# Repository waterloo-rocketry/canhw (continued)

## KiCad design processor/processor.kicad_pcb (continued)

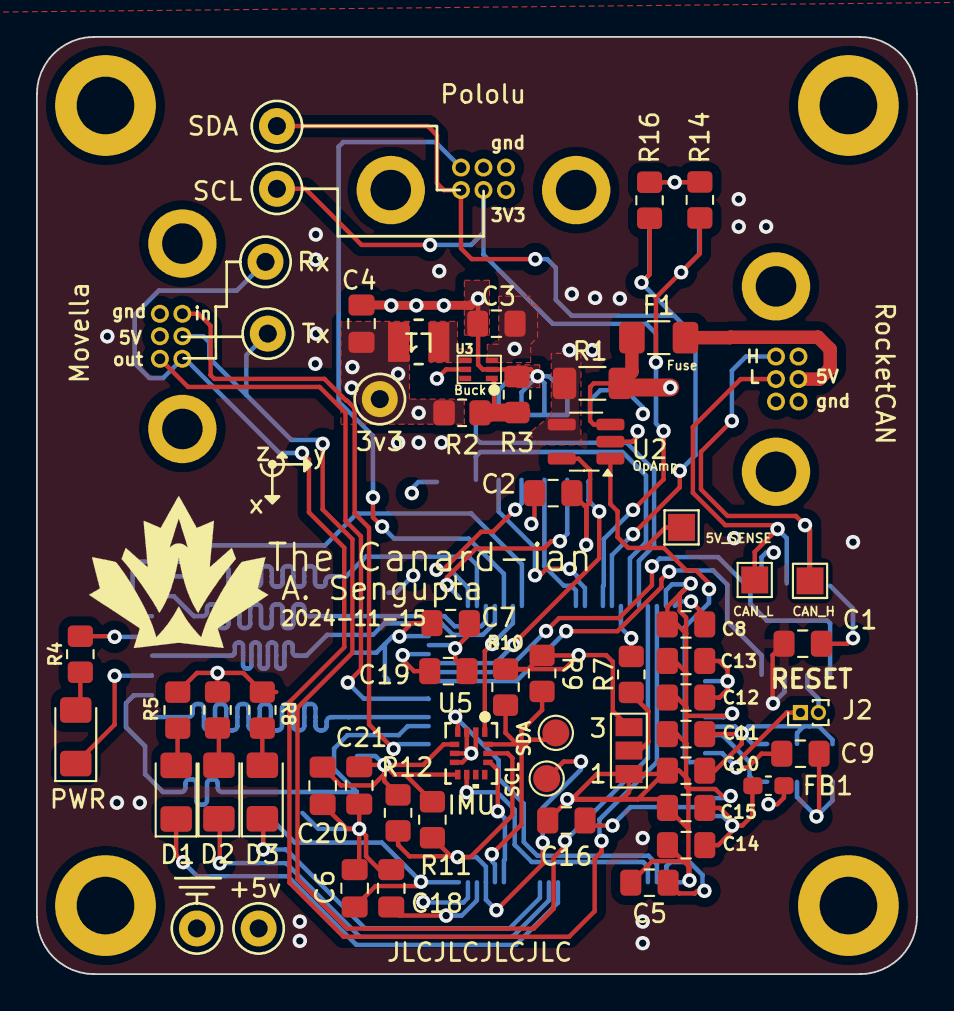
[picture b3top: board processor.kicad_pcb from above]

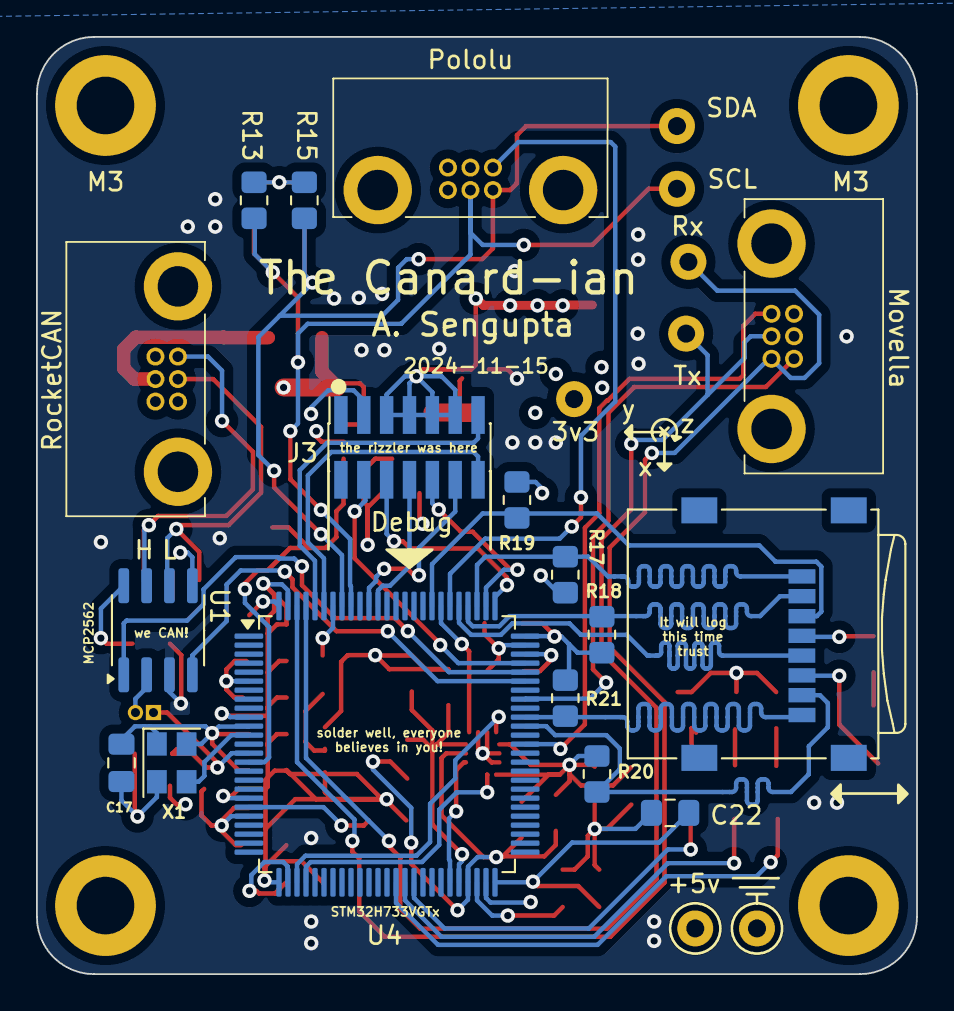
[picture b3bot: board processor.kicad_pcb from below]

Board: 4 copper layers, 48.9 x 52.1 mm, 79 parts (17 on the bottom side), 53 nets.

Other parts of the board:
H1, H2, H4: MountingHole_Pad; MountingHole_3.2mm_M3_DIN965_Pad

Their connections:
GND: H1.1, H2.1, H4.1; also elsewhere on the board

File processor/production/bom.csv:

Designator,Footprint,Quantity,Value,LCSC Part #
C1,0805,1,10uF,C15850
"C10, C22, C3",0805,3,4.7uF,C1779
"C11, C13, C15, C2, C20, C21, C5, C6, C7, C8, C9",0805,11,0.1uF,C49678
"C12, C14, C16",0805,3,1uF,C28323
C17,0805,1,0.01uF,C1710
"C18, C19",0805,2,2.2uF,C377773
C4,0805,1,22uF,C45783
D1,1206,1,LED_R,C7496845
D2,1206,1,LED_G,C7496843
D3,1206,1,LED_B,C434440
D4,1206,1,PWR,C434434
F1,1206,1,Polyfuse 1A,C20800
FB1,0603,1,PE-0603PFB121ST,C139186
L1,IND_DFE252012PD-1R0M=P2_MUR,1,1uH,C2917900
R1,1206,1,33 mR,C912764
"R10, R11, R12, R13, R14, R15, R16, R17, R18, R19, R20, R21, R7, R9",0805,14,10kΩ,C17414
R2,0805,1,453kΩ,C101739
R3,0805,1,100kΩ,C149504
"R4, R8",0805,2,150Ω,C17471
"R5, R6",0805,2,330Ω,C17630
U1,SOIC-8_3.9x4.9mm_P1.27mm,1,MCP2562,C191417
U2,SOT-23-5_HandSoldering,1,INA180,C2059240
U3,DRL0006A,1,TLV62568ADRLR,C398372
U4,LQFP-100_14x14mm_P0.5mm,1,STM32H733VGTx,C730160
U5,LGA-14L_2p5X3p0X0p86_STM,1,LSM6DSV16XTR,C5267406
X1,Oscillator_SMD_Abracon_ASE-4Pin_3.2x2.5mm,1,ASE-4.000MHZ-L-C-T,C437121

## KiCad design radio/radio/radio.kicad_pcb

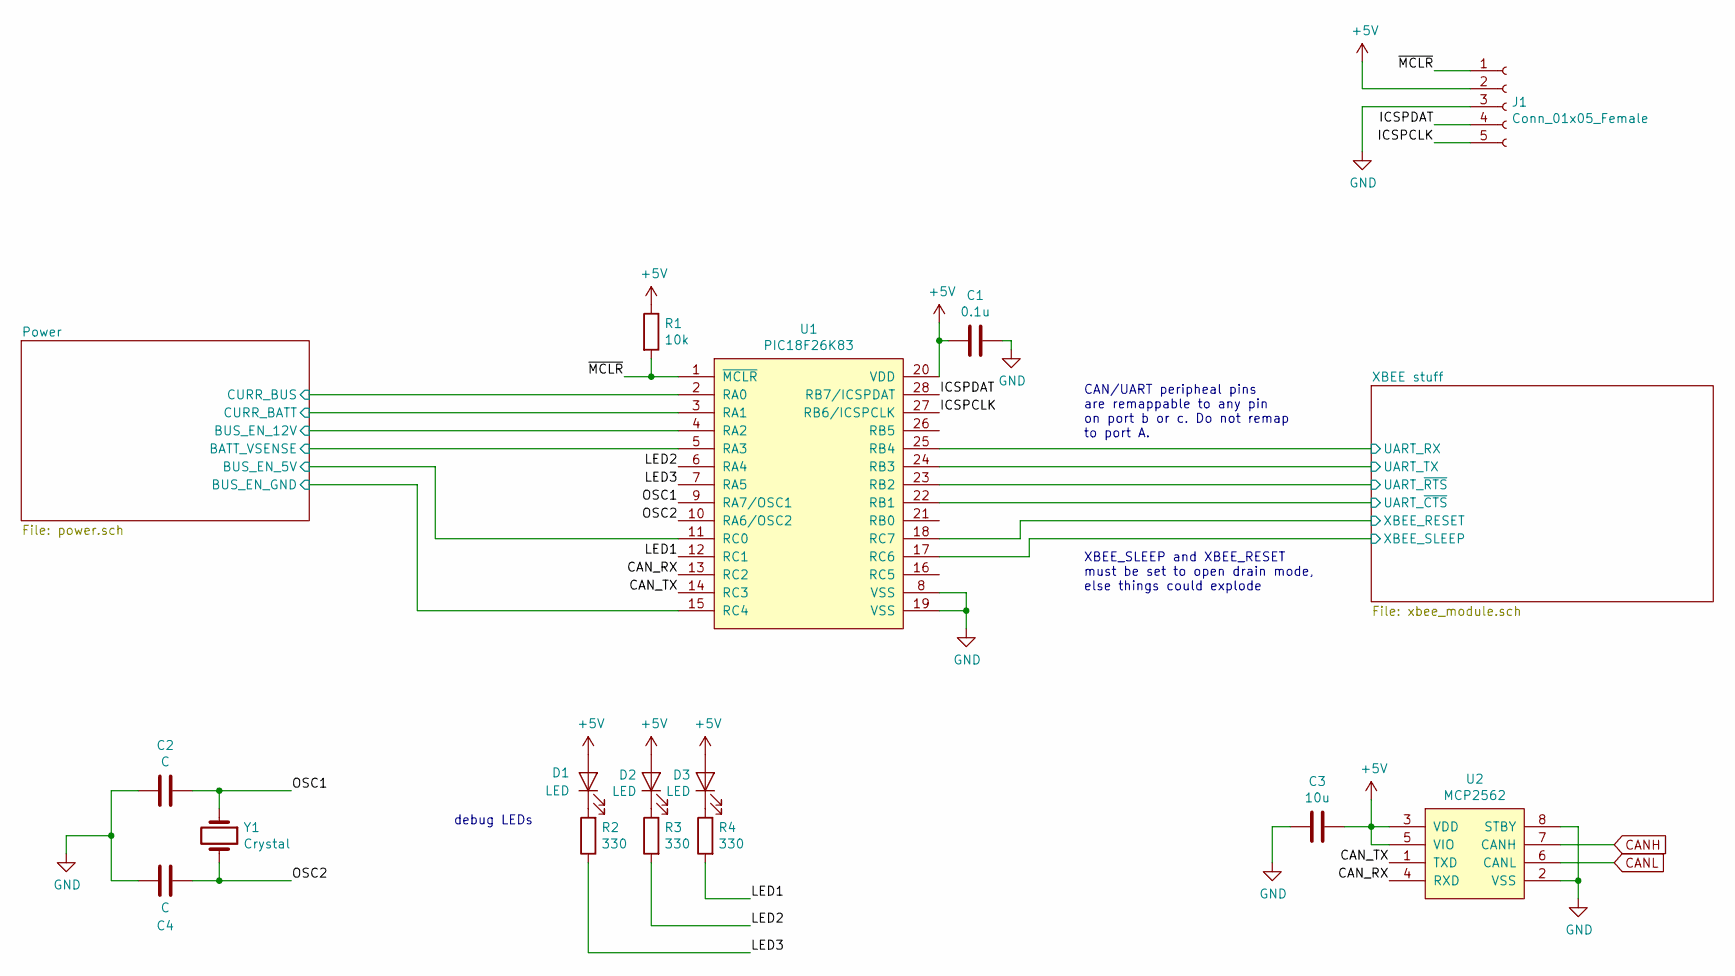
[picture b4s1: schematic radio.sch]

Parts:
C1: 0.1u; C_0805_2012Metric_Pad1.15x1.40mm_HandSolder
C2, C4: C; C_0805_2012Metric_Pad1.15x1.40mm_HandSolder
C3: 10u; C_0805_2012Metric_Pad1.15x1.40mm_HandSolder
D1, D2, D3: LED; LED_1206_3216Metric_Pad1.42x1.75mm_HandSolder
J1: Conn_01x05_Female; PinSocket_1x05_P2.54mm_Horizontal
R1: 10k; R_0805_2012Metric_Pad1.15x1.40mm_HandSolder
R2, R3, R4: 330; R_0805_2012Metric_Pad1.15x1.40mm_HandSolder
U1: PIC18F26K83; SOIC-28W_7.5x18.7mm_P1.27mm
U2: MCP2562; SOIC-8_3.9x4.9mm_P1.27mm
Y1: Crystal; Crystal_HC49-U_Vertical

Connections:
+5V: C1.2, C3.1, D1.2 (A), D2.2 (A), D3.2 (A), J1.2, R1.1, U1.20 (VDD), U2.3 (VDD), U2.5 (VIO); also elsewhere on the board
/CAN_RX: U1.13 (RC2), U2.4 (RXD)
/CAN_TX: U1.14 (RC3), U2.1 (TXD)
/ICSPCLK: J1.5, U1.27 (RB6/ICSPCLK)
/ICSPDAT: J1.4, U1.28 (RB7/ICSPDAT)
/LED1: R4.2, U1.12 (RC1)
/LED2: R3.2, U1.6 (RA4)
/LED3: R2.1, U1.7 (RA5)
/OSC1: C2.1, U1.9 (RA7/OSC1), Y1.1
/OSC2: C4.2, U1.10 (RA6/OSC2), Y1.2
/Power/BATT_VSENSE: U1.5 (RA3); also elsewhere on the board
/Power/BUS_EN_5V: U1.11 (RC0); also elsewhere on the board
/Power/BUS_EN_12V: U1.4 (RA2); also elsewhere on the board
/Power/BUS_EN_GND: U1.15 (RC4); also elsewhere on the board
/Power/CURR_BATT: U1.3 (RA1); also elsewhere on the board
/Power/CURR_BUS: U1.2 (RA0); also elsewhere on the board
/XBEE stuff/UART_RX: U1.25 (RB4); also elsewhere on the board
/XBEE stuff/UART_TX: U1.24 (RB3); also elsewhere on the board
/XBEE stuff/UART_~CTS: U1.22 (RB1); also elsewhere on the board
/XBEE stuff/UART_~RTS: U1.23 (RB2); also elsewhere on the board
/XBEE stuff/XBEE_RESET: U1.18 (RC7); also elsewhere on the board
/XBEE stuff/XBEE_SLEEP: U1.17 (RC6); also elsewhere on the board
/~MCLR: J1.1, R1.2, U1.1 (~MCLR)
CANH: U2.7 (CANH); also elsewhere on the board
CANL: U2.6 (CANL); also elsewhere on the board
GND: C1.1, C2.2, C3.2, C4.1, J1.3, U1.8 (VSS), U1.19 (VSS), U2.2 (VSS), U2.8 (STBY); also elsewhere on the board
unnamed: D1.1 (K), R2.2
unnamed: D2.1 (K), R3.1
unnamed: D3.1 (K), R4.1

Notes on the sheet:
CAN/UART peripheal pins are remappable to any pin on port b or c. Do not remap to port A.
XBEE_SLEEP and XBEE_RESET must be set to open drain mode, else things could explode
debug LEDs

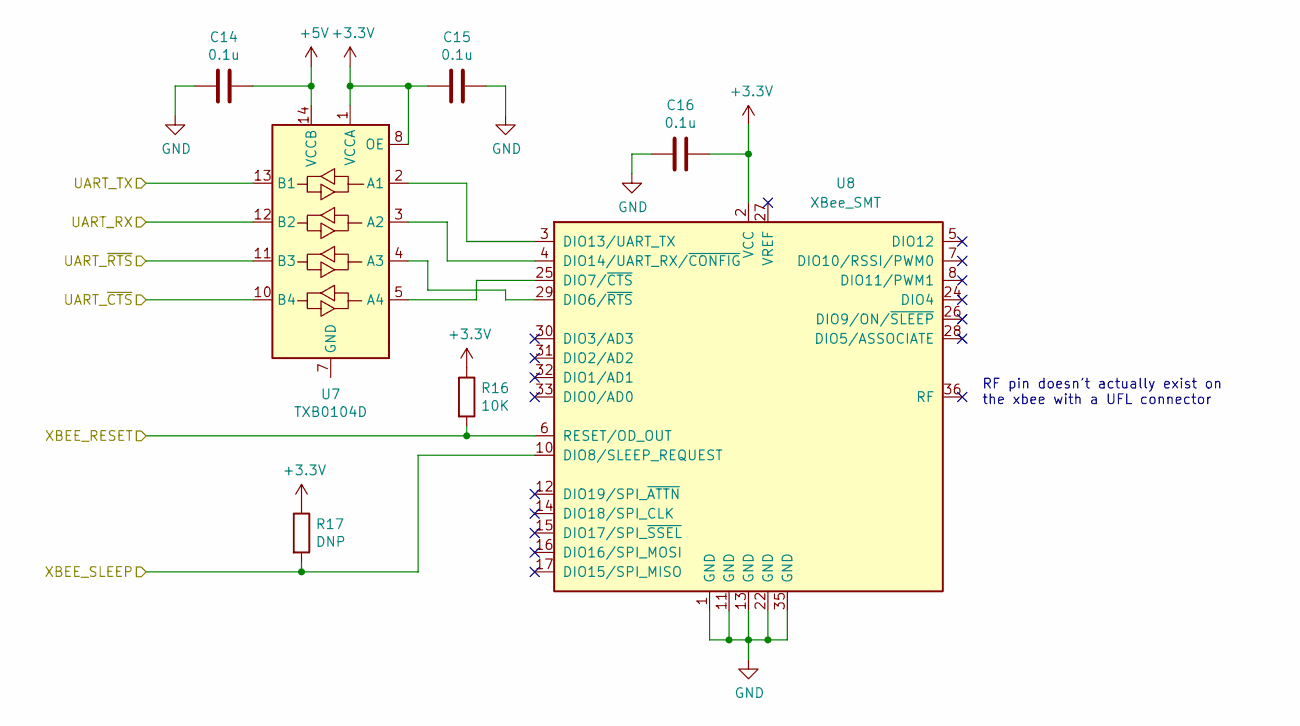
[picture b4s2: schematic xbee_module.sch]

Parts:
C14, C15, C16: 0.1u; C_0805_2012Metric_Pad1.15x1.40mm_HandSolder
R16: 10K; R_0805_2012Metric_Pad1.15x1.40mm_HandSolder
R17: DNP; R_0805_2012Metric_Pad1.15x1.40mm_HandSolder
U7: TXB0104D; SOIC-14_3.9x8.7mm_P1.27mm
U8: XBee_SMT; Digi_XBee_SMT

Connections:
+3V3: C15.2, C16.1, R16.1, R17.1, U7.1 (VCCA), U7.8 (OE), U8.2 (VCC); also elsewhere on the board
+5V: C14.1, U7.14 (VCCB); also elsewhere on the board
/XBEE stuff/UART_RX: U7.13 (B1); also elsewhere on the board
/XBEE stuff/UART_TX: U7.12 (B2); also elsewhere on the board
/XBEE stuff/UART_~CTS: U7.10 (B4); also elsewhere on the board
/XBEE stuff/UART_~RTS: U7.11 (B3); also elsewhere on the board
/XBEE stuff/XBEE_RESET: R16.2, U8.6 (RESET/OD_OUT); also elsewhere on the board
/XBEE stuff/XBEE_SLEEP: R17.2, U8.10 (DIO8/SLEEP_REQUEST); also elsewhere on the board
GND: C14.2, C15.1, C16.2, U8.1 (GND), U8.11 (GND), U8.13 (GND), U8.22 (GND), U8.35 (GND); also elsewhere on the board
unnamed: U7.4 (A3), U8.29 (DIO6/~RTS)
unnamed: U7.5 (A4), U8.25 (DIO7/~CTS)

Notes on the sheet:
RF pin doesn't actually exist on the xbee with a UFL connector

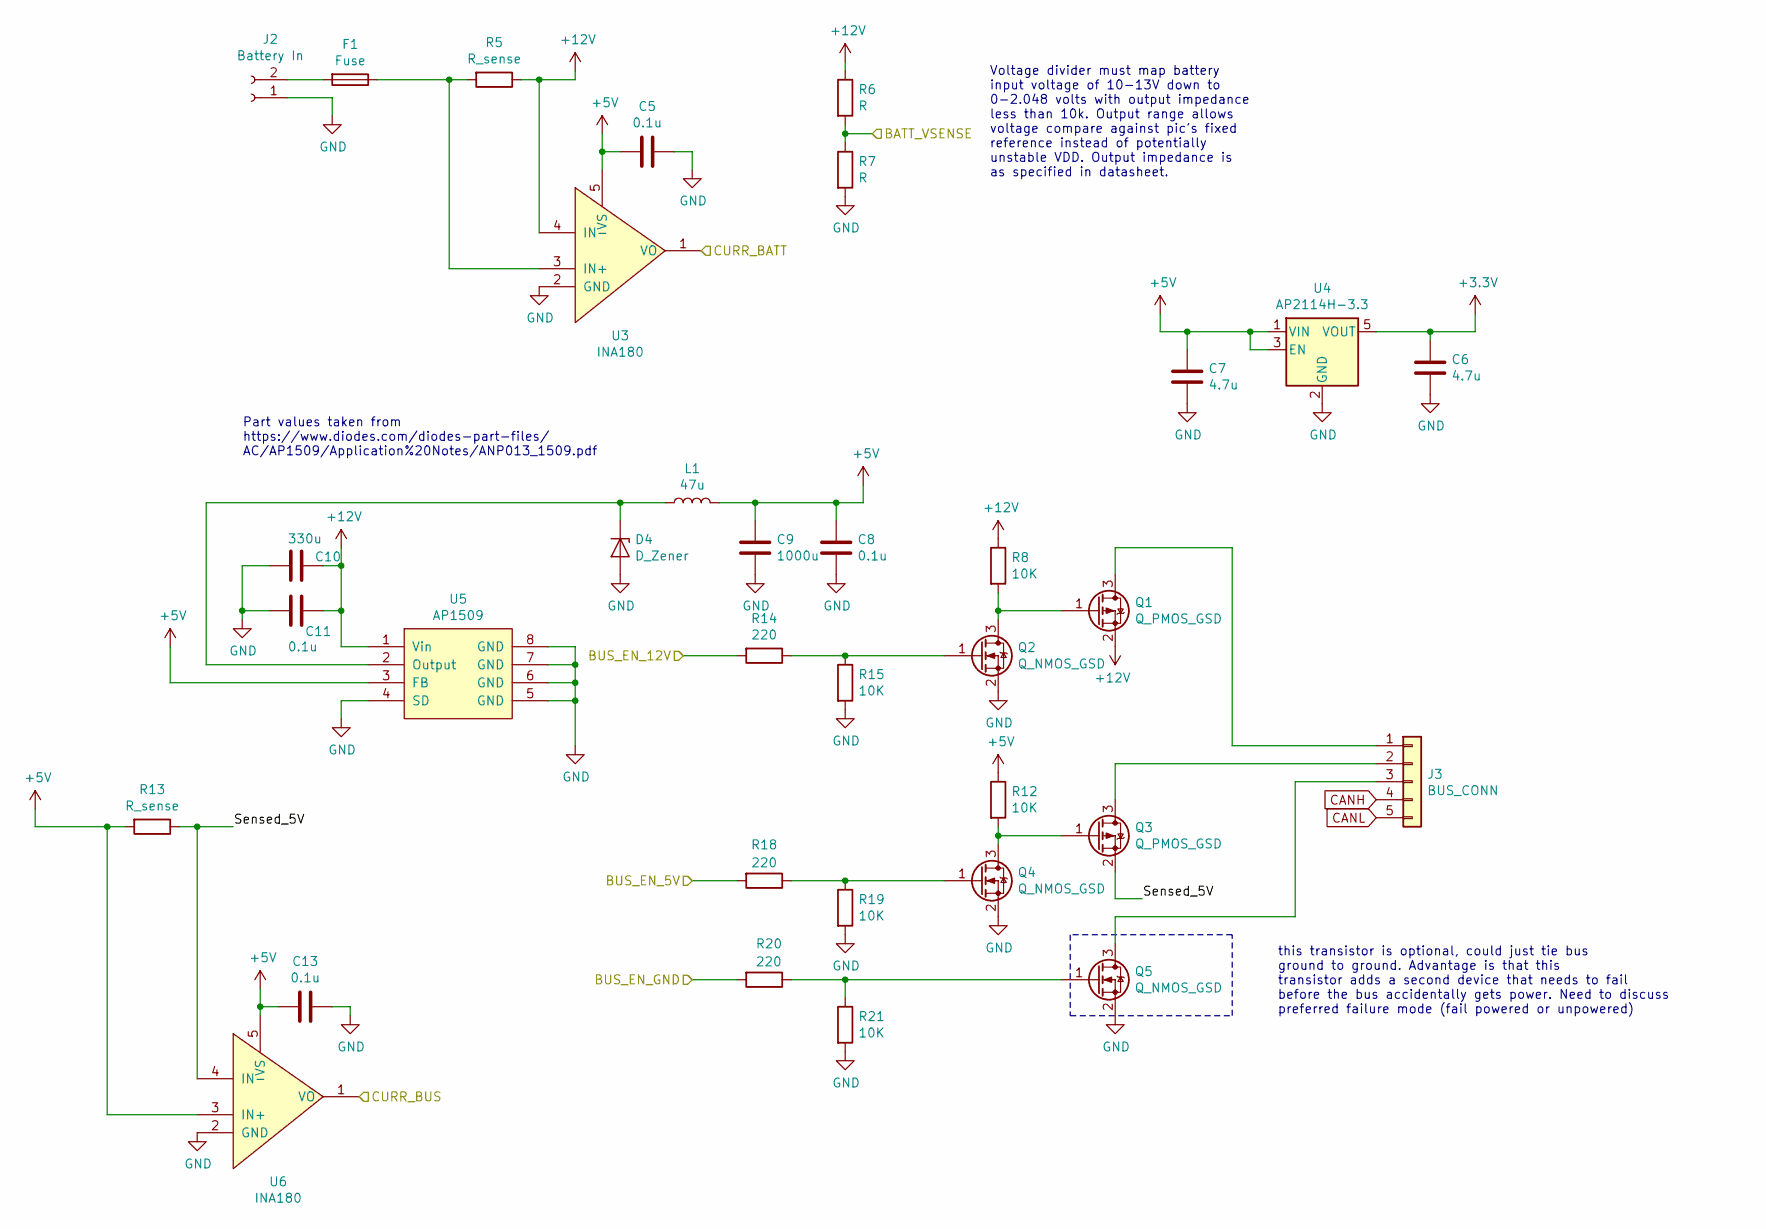
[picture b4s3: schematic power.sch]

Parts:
C5, C8, C11, C13: 0.1u; C_0805_2012Metric_Pad1.15x1.40mm_HandSolder
C6, C7: 4.7u; C_0805_2012Metric_Pad1.15x1.40mm_HandSolder
C9: 1000u; CP_Radial_D7.5mm_P2.50mm
C10: 330u; CP_Radial_D7.5mm_P2.50mm
D4: D_Zener; D_1206_3216Metric_Pad1.42x1.75mm_HandSolder
F1: Fuse; Fuseholder_36-3557-15-ND
J2: Battery In; BarrierBlock_ED2945-ND
J3: BUS_CONN; connector_Harwin_M80-5000642
L1: 47u; L_Radial_D8.7mm_P5.00mm_Fastron_07HCP
Q1, Q3: Q_PMOS_GSD; SOT-23_Handsoldering
Q2, Q4, Q5: Q_NMOS_GSD; SOT-23_Handsoldering
R5, R13: R_sense; R_1206_3216Metric_Pad1.42x1.75mm_HandSolder
R6, R7: R; R_0805_2012Metric_Pad1.15x1.40mm_HandSolder
R8, R12, R15, R19, R21: 10K; R_0805_2012Metric_Pad1.15x1.40mm_HandSolder
R14, R18, R20: 220; R_0805_2012Metric_Pad1.15x1.40mm_HandSolder
U3, U6: INA180; SOT-23-5_HandSoldering
U4: AP2114H-3.3; SOT-23-5_HandSoldering
U5: AP1509; SOIC-8_3.9x4.9mm_P1.27mm

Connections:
+3V3: C6.2, U4.5 (VOUT); also elsewhere on the board
+5V: C5.2, C7.2, C8.2, C9.2, C13.2, L1.2, R12.1, R13.2, U3.5 (VS), U4.1 (VIN), U4.3 (EN), U5.3 (FB), U6.3 (IN+), U6.5 (VS); also elsewhere on the board
+12V: C10.2, C11.2, Q1.2 (S), R5.1, R6.1, R8.1, U3.4 (IN-), U5.1 (Vin)
/Power/BATT_VSENSE: R6.2, R7.1; also elsewhere on the board
/Power/BUS_EN_5V: R18.2; also elsewhere on the board
/Power/BUS_EN_12V: R14.2; also elsewhere on the board
/Power/BUS_EN_GND: R20.2; also elsewhere on the board
/Power/CURR_BATT: U3.1 (VO); also elsewhere on the board
/Power/CURR_BUS: U6.1 (VO); also elsewhere on the board
/Power/Sensed_5V: Q3.2 (S), R13.1, U6.4 (IN-)
CANH: J3.4; also elsewhere on the board
CANL: J3.5; also elsewhere on the board
GND: C5.1, C6.1, C7.1, C8.1, C9.1, C10.1, C11.1, C13.1, D4.2 (A), J2.1, Q2.2 (S), Q4.2 (S), Q5.2 (S), R7.2, R15.2, R19.2, R21.2, U3.2 (GND), U4.2 (GND), U5.4 (SD), U5.5 (GND), U5.6 (GND), U5.7 (GND), U5.8 (GND), U6.2 (GND); also elsewhere on the board
unnamed: D4.1 (K), L1.1, U5.2 (Output)
unnamed: F1.1, R5.2, U3.3 (IN+)
unnamed: F1.2, J2.2
unnamed: J3.1, Q1.3 (D)
unnamed: J3.2, Q3.3 (D)
unnamed: J3.3, Q5.3 (D)
unnamed: Q1.1 (G), Q2.3 (D), R8.2
unnamed: Q2.1 (G), R14.1, R15.1
unnamed: Q3.1 (G), Q4.3 (D), R12.2
unnamed: Q4.1 (G), R18.1, R19.1
unnamed: Q5.1 (G), R20.1, R21.1

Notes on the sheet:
Voltage divider must map battery input voltage of 10-13V down to 0-2.048 volts with output impedance less than 10k. Output range allows voltage compare against pic's fixed reference instead of potentially unstable VDD. Output impedance is as specified in datasheet.
this transistor is optional, could just tie bus ground to ground. Advantage is that this transistor adds a second device that needs to fail before the bus accidentally gets power. Need to discuss preferred failure mode (fail powered or unpowered)
Part values taken from https://www.diodes.com/diodes-part-files/ AC/AP1509/Application%20Notes/ANP013_1509.pdf

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
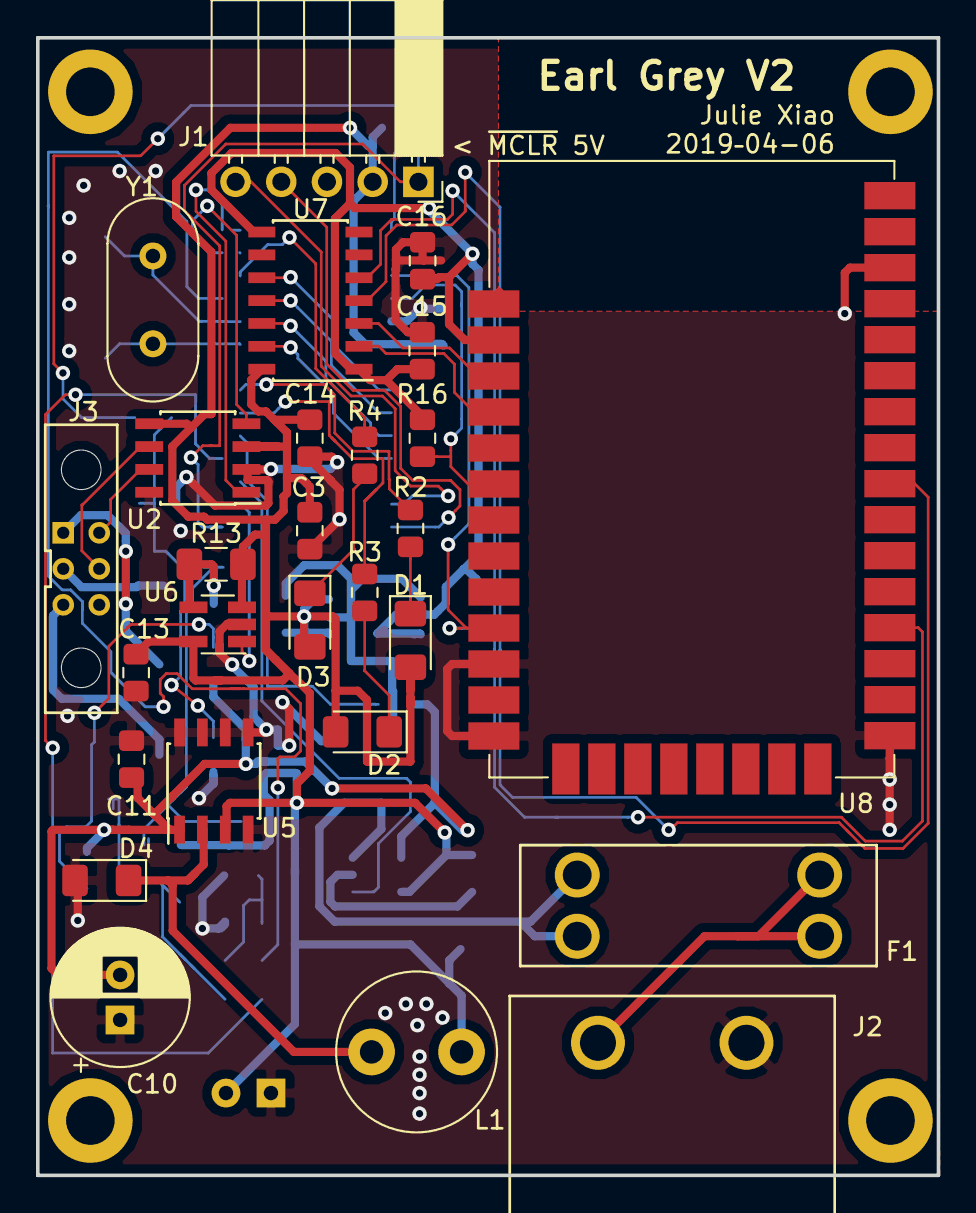
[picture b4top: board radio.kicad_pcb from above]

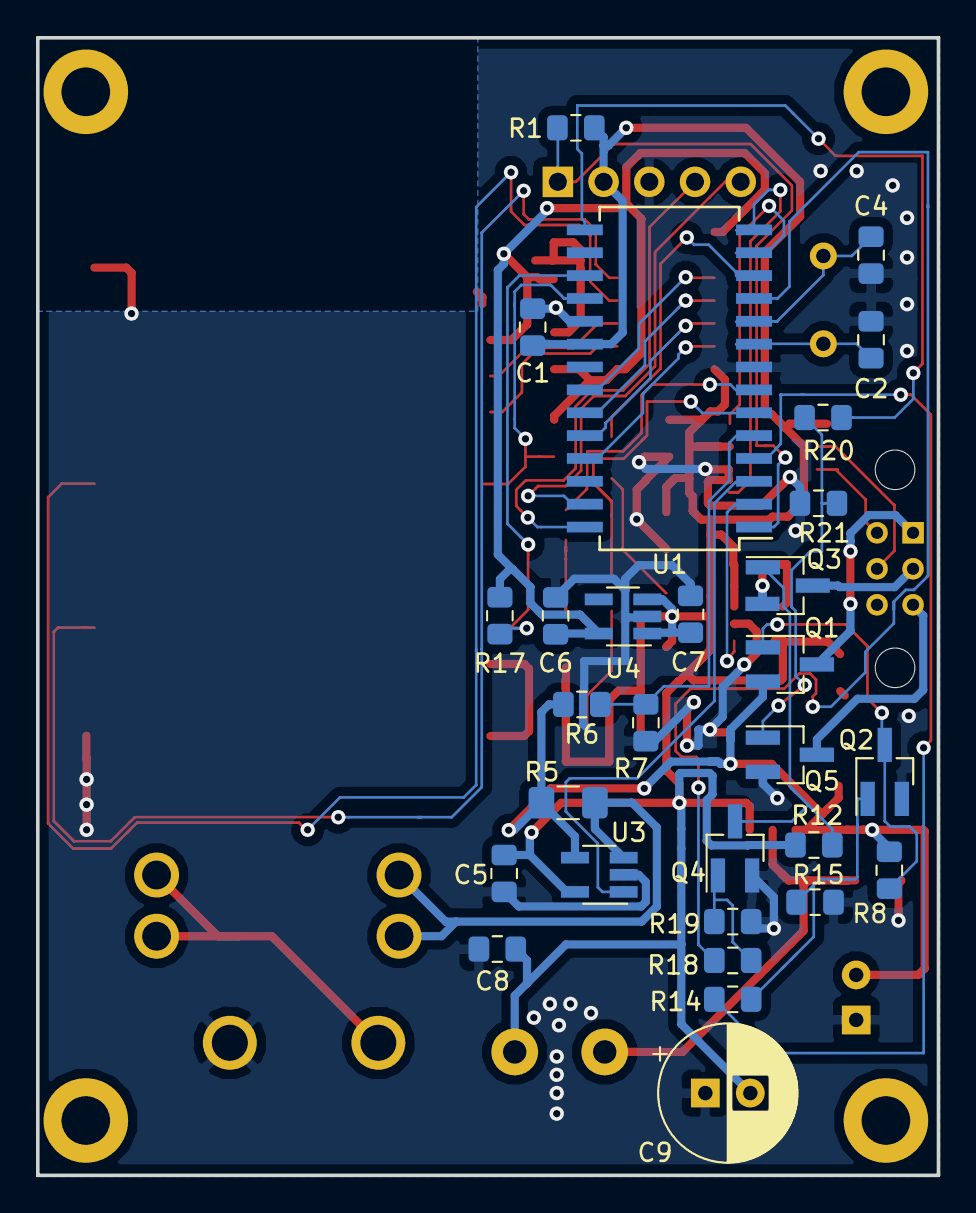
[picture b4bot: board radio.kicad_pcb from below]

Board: 2 copper layers, 50.0 x 63.2 mm, 56 parts (29 on the bottom side), 47 nets.

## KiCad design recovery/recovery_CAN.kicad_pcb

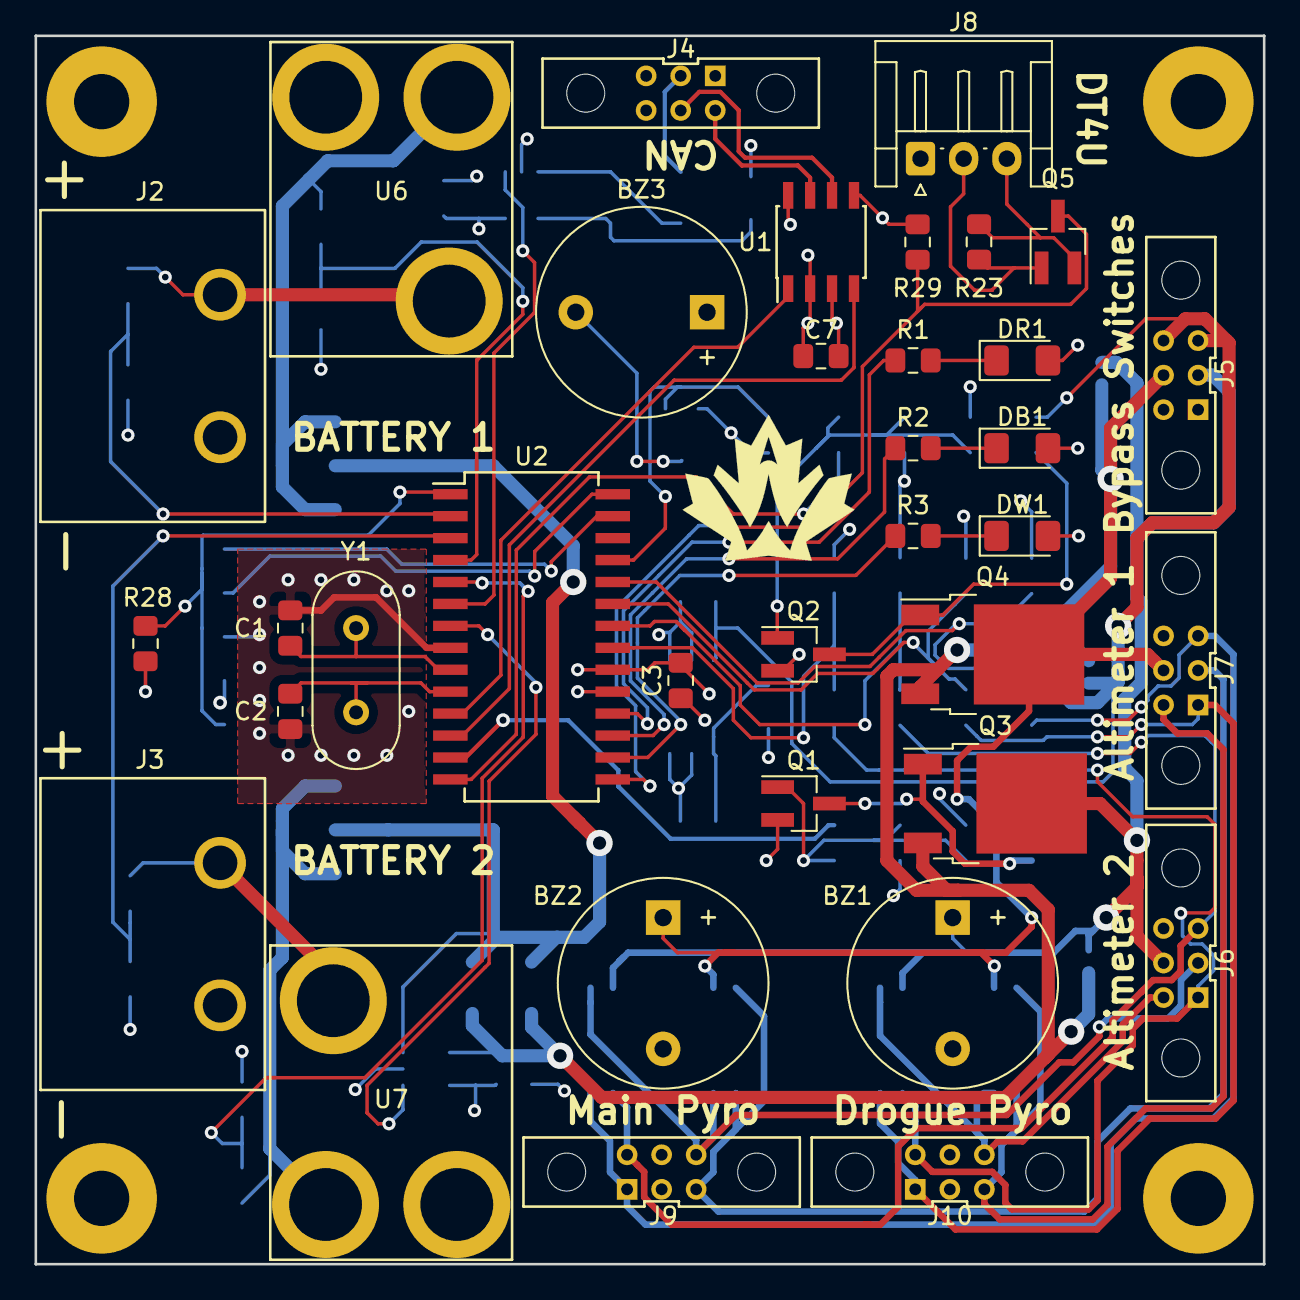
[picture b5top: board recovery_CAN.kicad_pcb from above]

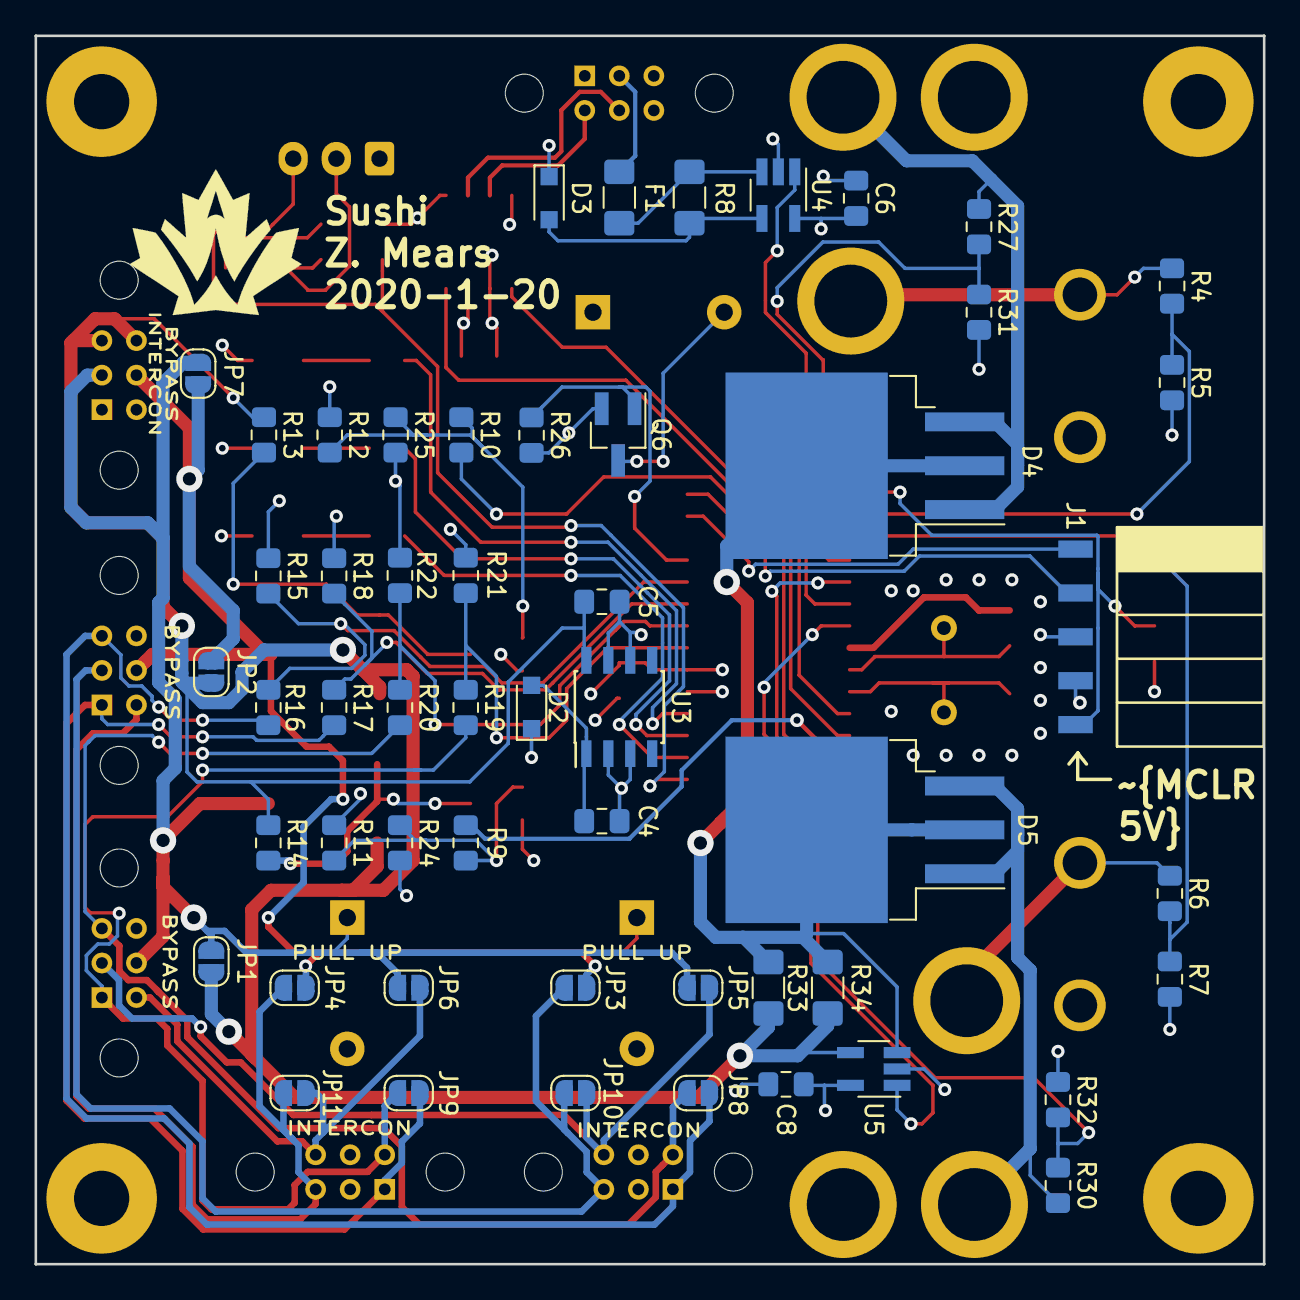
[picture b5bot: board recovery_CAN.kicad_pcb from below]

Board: 4 copper layers, 71.1 x 71.1 mm, 88 parts (53 on the bottom side), 58 nets.

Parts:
BZ1: WST-1212BX; Buzzer_12x9.5RM7.6
BZ2: CMI-1295-1285T; Buzzer_12x9.5RM7.6
BZ3: CMI-1295-0585T; Buzzer_12x9.5RM7.6
C1, C2: 27pF; C_0805_2012Metric_Pad1.15x1.40mm_HandSolder
C3: 0.1u; C_0805_2012Metric_Pad1.15x1.40mm_HandSolder
C4, C6, C8: 0.1uF; C_0805_2012Metric_Pad1.15x1.40mm_HandSolder
C5: 0.33uF; C_0805_2012Metric_Pad1.15x1.40mm_HandSolder
C7: 10uF; C_0805_2012Metric_Pad1.15x1.40mm_HandSolder
D2, D3: CUS08F30; D_SOD-323_HandSoldering
D4, D5: SM74611
DB1: LED; LED_1206_3216Metric_Pad1.42x1.75mm_HandSolder
DR1: LED; LED_1206_3216Metric_Pad1.42x1.75mm_HandSolder
DW1: LED; LED_1206_3216Metric_Pad1.42x1.75mm_HandSolder
F1: Polyfuse; Fuse_1206_3216Metric_Pad1.42x1.75mm_HandSolder
J1: Conn_01x05_Female; PinHeader_5x2.54_SMD_90deg_952-3198-1-ND
J2: Battery 1; BarrierBlock_ED2945-ND
J3: Battery 2; BarrierBlock_ED2945-ND
J4: CAN connector; connector_Harwin_M80-5000642
J5: Bypass Mag Switches; connector_Harwin_M80-5000642
J6: A2 Connector; connector_Harwin_M80-5000642
J7: A1 Connector; connector_Harwin_M80-5000642
J8: SL Data Connector; JST_EH_S03B-EH_1x03_P2.50mm_Horizontal
J9: Main Pyros; connector_Harwin_M80-5000642
J10: Drogue Pyro; connector_Harwin_M80-5000642
JP1, JP2: Bypass Jumper; SolderJumper-2_P1.3mm_Open_RoundedPad1.0x1.5mm
JP3: M1 Pull Up; SolderJumper-2_P1.3mm_Open_RoundedPad1.0x1.5mm
JP4: D1 Pull Up; SolderJumper-2_P1.3mm_Open_RoundedPad1.0x1.5mm
JP5: M2 Pull Up; SolderJumper-2_P1.3mm_Open_RoundedPad1.0x1.5mm
JP6: D2 Pull Up; SolderJumper-2_P1.3mm_Open_RoundedPad1.0x1.5mm
JP7: Bypass tie together; SolderJumper-2_P1.3mm_Open_RoundedPad1.0x1.5mm
JP8, JP9: Pyro Interconnect; SolderJumper-2_P1.3mm_Open_RoundedPad1.0x1.5mm
JP10, JP11: Pyro Interconect; SolderJumper-2_P1.3mm_Open_RoundedPad1.0x1.5mm
Q1, Q2: DMG2302UK; SOT-23_Handsoldering
Q3, Q4: AOD417; TO-252-2
Q5, Q6: BSS138; SOT-23_Handsoldering
R1, R2, R3: 330R; R_0805_2012Metric_Pad1.15x1.40mm_HandSolder
R4, R6, R27, R30: 27K; R_0805_2012Metric_Pad1.15x1.40mm_HandSolder
R5, R7, R23, R26, R28, R29, R31, R32: 10K; R_0805_2012Metric_Pad1.15x1.40mm_HandSolder
R8: 200mR; R_1206_3216Metric_Pad1.42x1.75mm_HandSolder
R9, R10: 270R; R_0805_2012Metric_Pad1.15x1.40mm_HandSolder
R11, R12, R15, R18, R21, R22: 10k; R_0805_2012Metric_Pad1.15x1.40mm_HandSolder
R13, R14: 15k; R_0805_2012Metric_Pad1.15x1.40mm_HandSolder
R16, R17, R19, R20: 27k; R_0805_2012Metric_Pad1.15x1.40mm_HandSolder
R24, R25: DNP; R_0805_2012Metric_Pad1.15x1.40mm_HandSolder
R33, R34: 8mR; R_1206_3216Metric_Pad1.42x1.75mm_HandSolder
U1: MCP2562; SOIC-8_3.9x4.9mm_P1.27mm
U2: PIC18F26K83; SOIC-28W_7.5x18.7mm_P1.27mm
U3: L78L05AC; SOIC-8_3.9x4.9mm_P1.27mm
U4, U5: INA180; SOT-23-5_HandSoldering
U6, U7: Mag Switch
Y1: Crystal; Crystal_HC49-4H_Vertical

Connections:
+5V: BZ3.1, C3.2, C6.2, C7.1, C8.2, D2.1, D3.1, DB1.2, DR1.2, DW1.2, J1.4, R11.1, R12.1, R28.1, R29.1, U1.3, U1.5, U2.20, U4.5, U5.5
+BATT: C5.1, J5.3, J5.6, JP1.1, JP2.1, Q3.3, Q4.3, R13.1, R14.1, R33.1, R34.1, U3.8, U5.4
/CAN_RX: U1.4, U2.12
/CAN_TX: U1.1, U2.11
/ICSPCLK: J1.1, U2.27
/ICSPDAT: J1.2, U2.28
/LED1: R3.2, U2.16
/LED2: R2.2, U2.17
/LED3: R1.2, U2.18
/OSC1: C1.1, U2.9, Y1.1
/OSC2: C2.1, U2.10, Y1.2
/altimeters/A1_ARM: R10.2, U2.14
/altimeters/A1_DROGUE: R17.1, R18.2, U2.23
/altimeters/A1_MAIN: R15.2, R16.2, U2.24
/altimeters/A2_ARM: R9.2, U2.13
/altimeters/A2_DROGUE: R19.1, R21.1, U2.21
/altimeters/A2_MAIN: R20.1, R22.1, U2.22
/altimeters/D1+: J7.4, J10.3, JP4.1, JP11.1
/altimeters/D1_PYRO: J7.1, J10.1, JP9.1, R17.2
/altimeters/D2+: J6.4, J10.6, JP6.1, JP11.2
/altimeters/D2_PYRO: J6.1, J10.4, JP9.2, R19.2
/altimeters/M1+: J7.2, J9.3, JP3.1, JP10.1
/altimeters/M1_PYRO: J7.3, J9.1, JP8.1, R16.1
/altimeters/M2+: J6.2, J9.6, JP5.1, JP10.2
/altimeters/M2_PYRO: J6.3, J9.4, JP8.2, R20.2
/altimeters/SL_TX: Q5.3, R29.2, U2.15
/power/CURR_AMP_BATT: U2.7, U5.1
/power/CURR_AMP_CAN: U2.6, U4.1
/power/RAW_BAT: D4.1, D5.1, R33.2, R34.2, U5.3
/power/VBAT1: R4.2, R5.1, U2.2
/power/VBAT2: R6.2, R7.1, U2.3
/power/VMAG1: R27.1, R31.1, U2.4
/power/VMAG2: R30.1, R32.1, U2.5
/~MCLR: J1.5, R28.2, U2.1
CANH: J4.4, U1.7
CANL: J4.5, U1.6
GND: BZ1.2, BZ2.2, C1.2, C2.2, C3.1, C4.2, C5.2, C6.1, C7.2, C8.1, J1.3, J2.1, J3.1, J4.3, J5.1, J5.4, J6.6, J7.6, J8.1, Q1.2, Q2.2, Q6.2, R5.2, R7.2, R15.1, R18.1, R21.2, R22.2, R24.2, R25.2, R26.2, R31.2, R32.2, U1.2, U1.8, U2.8, U2.19, U3.2, U3.3, U3.6, U3.7, U4.2, U5.2, U6.3, U7.3
unnamed: BZ1.1, J5.2, J6.5, JP1.2, JP5.2, JP6.2, JP7.2, Q3.2
unnamed: BZ2.1, J5.5, J7.5, JP2.2, JP3.2, JP4.2, JP7.1, Q4.2
unnamed: BZ3.2, Q6.3
unnamed: C4.1, D2.2, U3.1
unnamed: D3.2, R8.1, U4.4
unnamed: D4.2, R27.2, U6.2
unnamed: D5.2, R30.2, U7.2
unnamed: DB1.1, R2.1
unnamed: DR1.1, R1.1
unnamed: DW1.1, R3.1
unnamed: F1.1, R8.2, U4.3
unnamed: F1.2, J4.2
unnamed: J2.2, R4.1, U6.1
unnamed: J3.2, R6.1, U7.1
unnamed: J8.2, Q5.1, R23.1
unnamed: J8.3, Q5.2, R23.2
unnamed: Q1.1, R9.1, R11.2, R24.1
unnamed: Q1.3, Q3.1, R14.2
unnamed: Q2.1, R10.1, R12.2, R25.1
unnamed: Q2.3, Q4.1, R13.2
unnamed: Q6.1, R26.1, U2.25
